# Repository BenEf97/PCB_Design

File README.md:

# PCB_Design
 My PCB designs

Projects:
1. STM32F4 REV2 - STM32 Microcontroller + USB + Buck Converter PCB Design, guided by Phil's Lab. Use link for reference:
   https://fedevel.com/blog/kicad-stm32-usb-buck-converter-pcb-design-and-jlcpcb-assembly-update-phils-lab-11

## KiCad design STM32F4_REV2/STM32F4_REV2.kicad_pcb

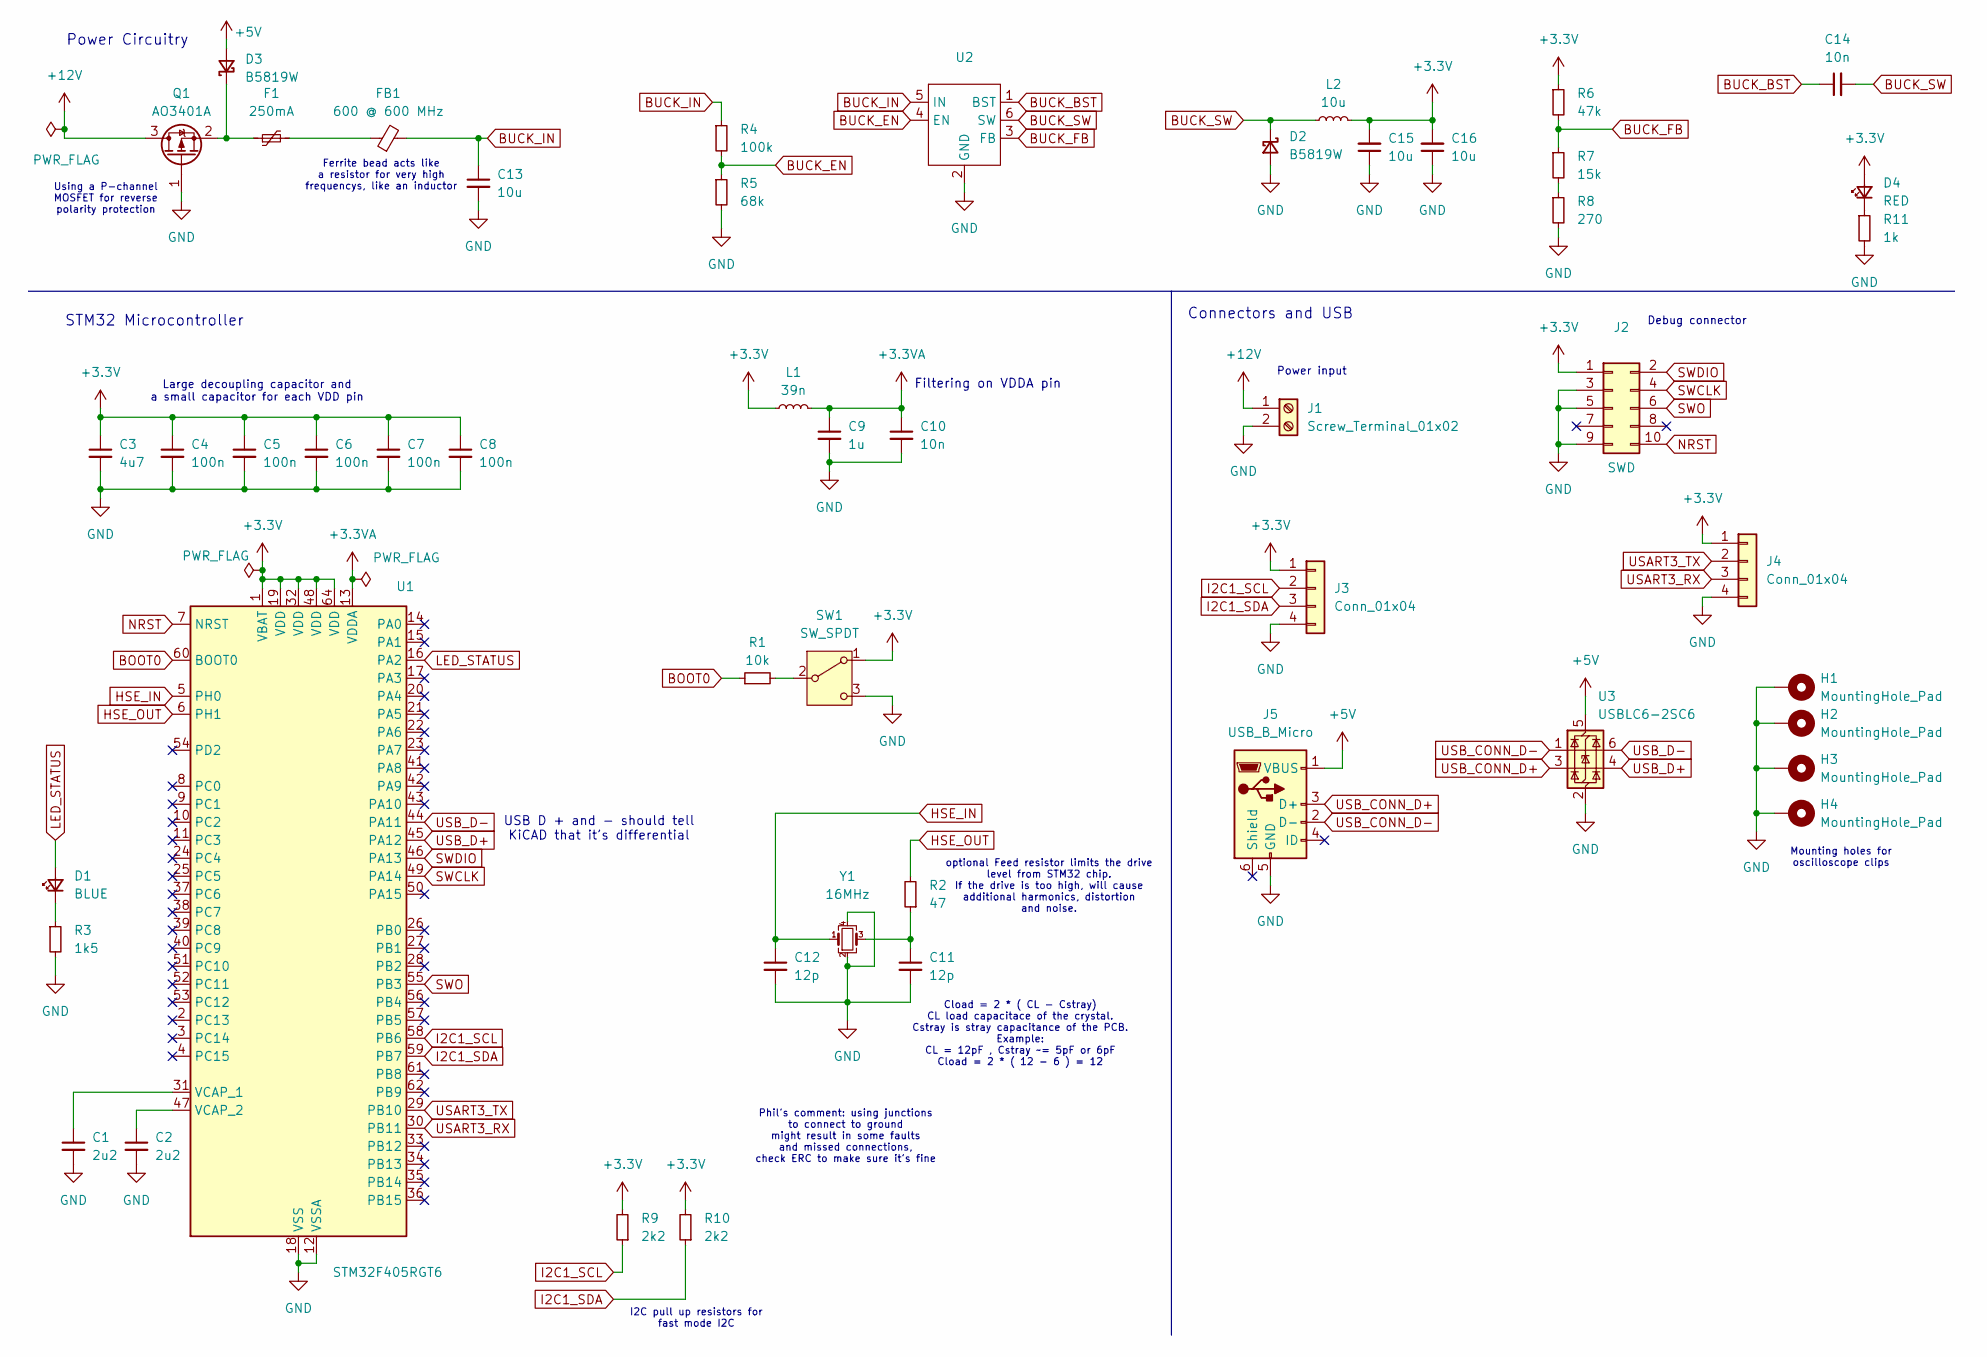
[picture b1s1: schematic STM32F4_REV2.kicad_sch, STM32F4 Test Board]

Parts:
C1, C2: 2u2; C_0603_1608Metric
C3: 4u7; C_0603_1608Metric
C4, C5, C6, C7, C8: 100n; C_0402_1005Metric
C9: 1u; C_0402_1005Metric
C10: 10n; C_0402_1005Metric
C11, C12: 12p; C_0402_1005Metric
C13, C15, C16: 10u; C_1206_3216Metric
C14: 10n; C_0603_1608Metric
D1: BLUE; LED_0603_1608Metric
D2, D3: B5819W; D_SOD-123
D4: RED; LED_0603_1608Metric
F1: 250mA; Fuse_1206_3216Metric
FB1: 600 @ 600 MHz; L_0805_2012Metric
H1, H2, H3, H4: MountingHole_Pad; MountingHole_4.3mm_M4_Pad_Via
J1: Screw_Terminal_01x02; TerminalBlock_Phoenix_PT-1,5-2-3.5-H_1x02_P3.50mm_Horizontal
J2: SWD; PinSocket_2x05_P1.27mm_Vertical_SMD
J3, J4: Conn_01x04; Molex_PicoBlade_53048-0410_1x04_P1.25mm_Horizontal
J5: USB_B_Micro; USB_Micro-B_Amphenol_10118193-0001LF_Horizontal
L1: 39n; L_0402_1005Metric
L2: 10u; L_Sunlord_MWSA0503S
Q1: AO3401A; SOT-23
R1: 10k; R_0402_1005Metric
R2: 47; R_0402_1005Metric
R3: 1k5; R_0603_1608Metric
R4: 100k; R_0603_1608Metric
R5: 68k; R_0603_1608Metric
R6: 47k; R_0603_1608Metric
R7: 15k; R_0603_1608Metric
R8: 270; R_0603_1608Metric
R9, R10: 2k2; R_0402_1005Metric
R11: 1k; R_0603_1608Metric
SW1: SW_SPDT; SW_SPDT_PCM12
U1: STM32F405RGT6; LQFP-64_10x10mm_P0.5mm
U2: SOT-23-6
U3: USBLC6-2SC6; SOT-23-6
Y1: 16MHz; Crystal_SMD_3225-4Pin_3.2x2.5mm

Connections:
+3.3V: C3.1, C4.1, C5.1, C6.1, C7.1, C8.1, C15.2, C16.2, D4.2 (A), J2.1, J3.1, J4.1, L1.1, L2.2, R6.1, R9.2, R10.2, SW1.1 (A), U1.1 (VBAT), U1.19 (VDD), U1.32 (VDD), U1.48 (VDD), U1.64 (VDD)
+3.3VA: C9.1, C10.1, L1.2, U1.13 (VDDA)
+5V: D3.2 (A), J5.1 (VBUS), U3.5 (VBUS)
+12V: J1.1, Q1.3 (D)
BOOT0: R1.1, U1.60 (BOOT0)
BUCK_BST: C14.1, U2.1 (BST)
BUCK_EN: R4.2, R5.1, U2.4 (EN)
BUCK_FB: R6.2, R7.1, U2.3 (FB)
BUCK_IN: C13.1, FB1.2, R4.1, U2.5 (IN)
BUCK_SW: C14.2, D2.1 (K), L2.1, U2.6 (SW)
GND: C1.2, C2.2, C3.2, C4.2, C5.2, C6.2, C7.2, C8.2, C9.2, C10.2, C11.2, C12.2, C13.2, C15.1, C16.1, D2.2 (A), H1.1, H2.1, H3.1, H4.1, J1.2, J2.3, J2.5, J2.9, J3.4, J4.4, J5.5 (GND), Q1.1 (G), R3.2, R5.2, R8.2, R11.2, SW1.3 (C), U1.12 (VSSA), U1.18 (VSS), U1.63 (VSS), U2.2 (GND), U3.2 (GND), Y1.2, Y1.4
HSE_IN: C12.1, U1.5 (PH0), Y1.1
HSE_OUT: R2.2, U1.6 (PH1)
I2C1_SCL: J3.2, R9.1, U1.58 (PB6)
I2C1_SDA: J3.3, R10.1, U1.59 (PB7)
LED_STATUS: D1.2 (A), U1.16 (PA2)
NRST: J2.10, U1.7 (NRST)
unnamed: C11.1, R2.1, Y1.3
unnamed: D1.1 (K), R3.1
unnamed: D3.1 (K), F1.1, Q1.2 (S)
unnamed: D4.1 (K), R11.1
unnamed: F1.2, FB1.1
unnamed: R7.2, R8.1
unnamed: R1.2, SW1.2 (B)
unnamed: C1.1, U1.31 (VCAP_1)
unnamed: C2.1, U1.47 (VCAP_2)
SWCLK: J2.4, U1.49 (PA14)
SWDIO: J2.2, U1.46 (PA13)
SWO: J2.6, U1.55 (PB3)
USART3_RX: J4.3, U1.30 (PB11)
USART3_TX: J4.2, U1.29 (PB10)
USB_CONN_D+: J5.3 (D+), U3.3 (I/O2)
USB_CONN_D-: J5.2 (D-), U3.1 (I/O1)
USB_D+: U1.45 (PA12), U3.4 (I/O2)
USB_D-: U1.44 (PA11), U3.6 (I/O1)

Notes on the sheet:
Ferrite bead acts like a resistor for very high frequencys, like an inductor
STM32 Microcontroller
Mounting holes for oscilloscope clips
Filtering on VDDA pin
Power Circuitry
USB D + and - should tell KiCAD that it's differential
Using a P-channel MOSFET for reverse polarity protection
Phil's comment: using junctions to connect to ground might result in some faults and missed connections, check ERC to make sure it's fine
Connectors and USB
Large decoupling capacitor and a small capacitor for each VDD pin
Power input
I2C pull up resistors for fast mode I2C
Debug connector
Cload = 2 * ( CL - Cstray) CL load capacitace of the crystal. Cstray is stray capacitance of the PCB. Example: CL = 12pF , Cstray ~= 5pF or 6pF Cload = 2 * ( 12 - 6 ) = 12
optional Feed resistor limits the drive level from STM32 chip. If the drive is too high, will cause additional harmonics, distortion and noise.

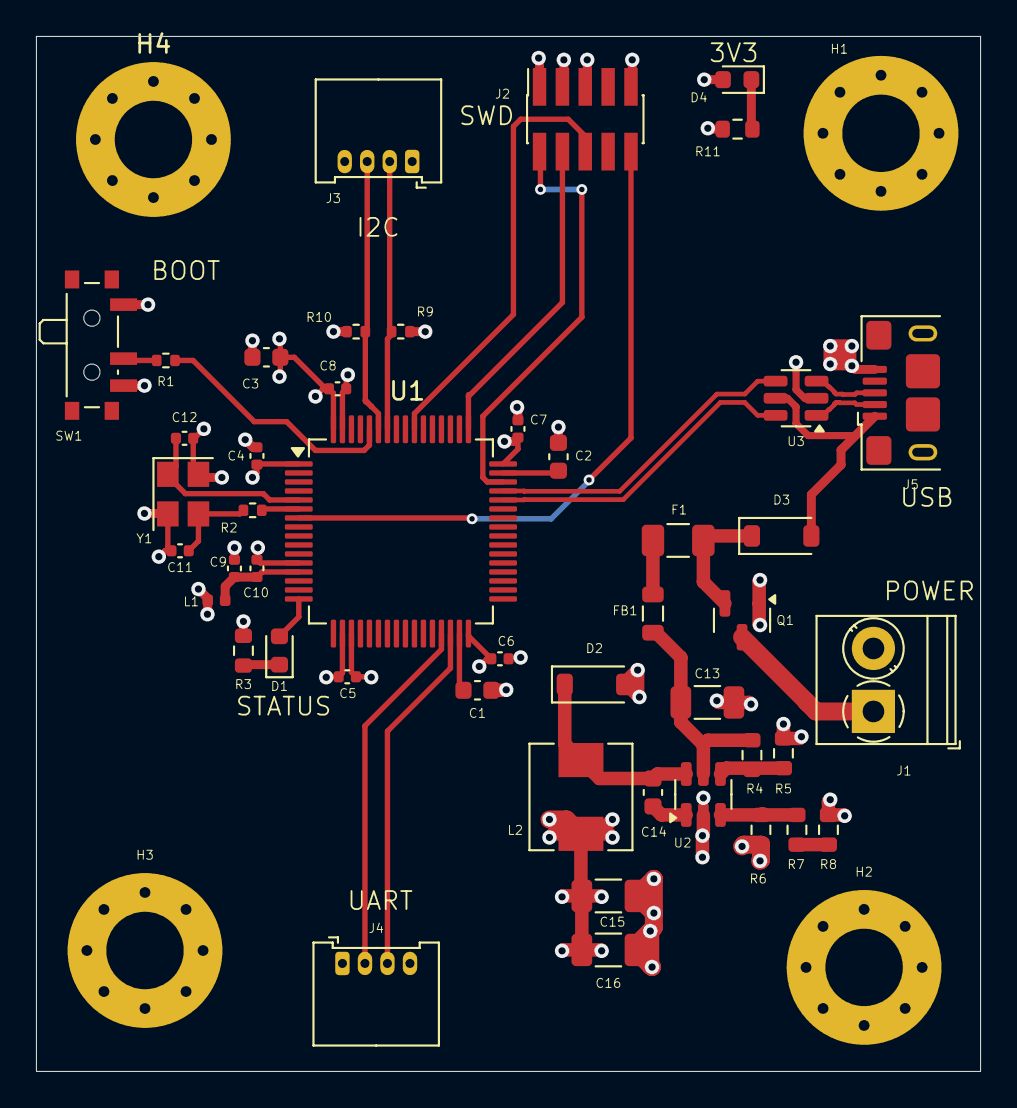
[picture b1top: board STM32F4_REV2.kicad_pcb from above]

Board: 4 copper layers, 52.5 x 57.5 mm, 50 parts (0 on the bottom side), 35 nets.

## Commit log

2024-08-29 STM32F4_REV2 Start
    Started doing the KiCAD STM32 + USB + Buck Converter PCB Design.
    Finished STM32 Microcontroller schematic and Power Circuitry.
2024-08-29 Finished Footprints
    Finished selecting footprints.
    Used Phi'ls selections but for USB Micro B I found in my own.
2024-08-30 Layout finished
    Finished the layout, need to route
2024-09-02 Finished routing
